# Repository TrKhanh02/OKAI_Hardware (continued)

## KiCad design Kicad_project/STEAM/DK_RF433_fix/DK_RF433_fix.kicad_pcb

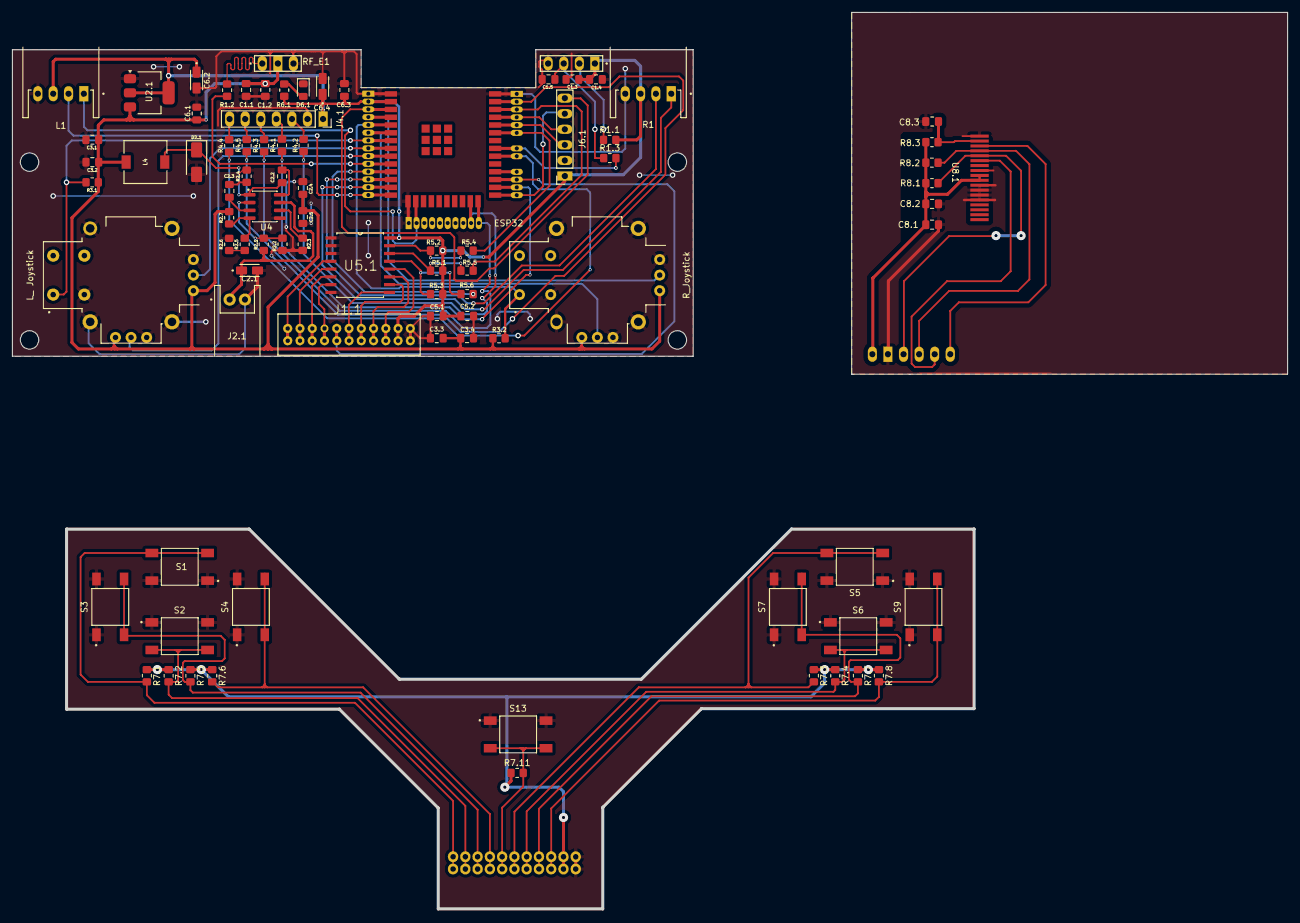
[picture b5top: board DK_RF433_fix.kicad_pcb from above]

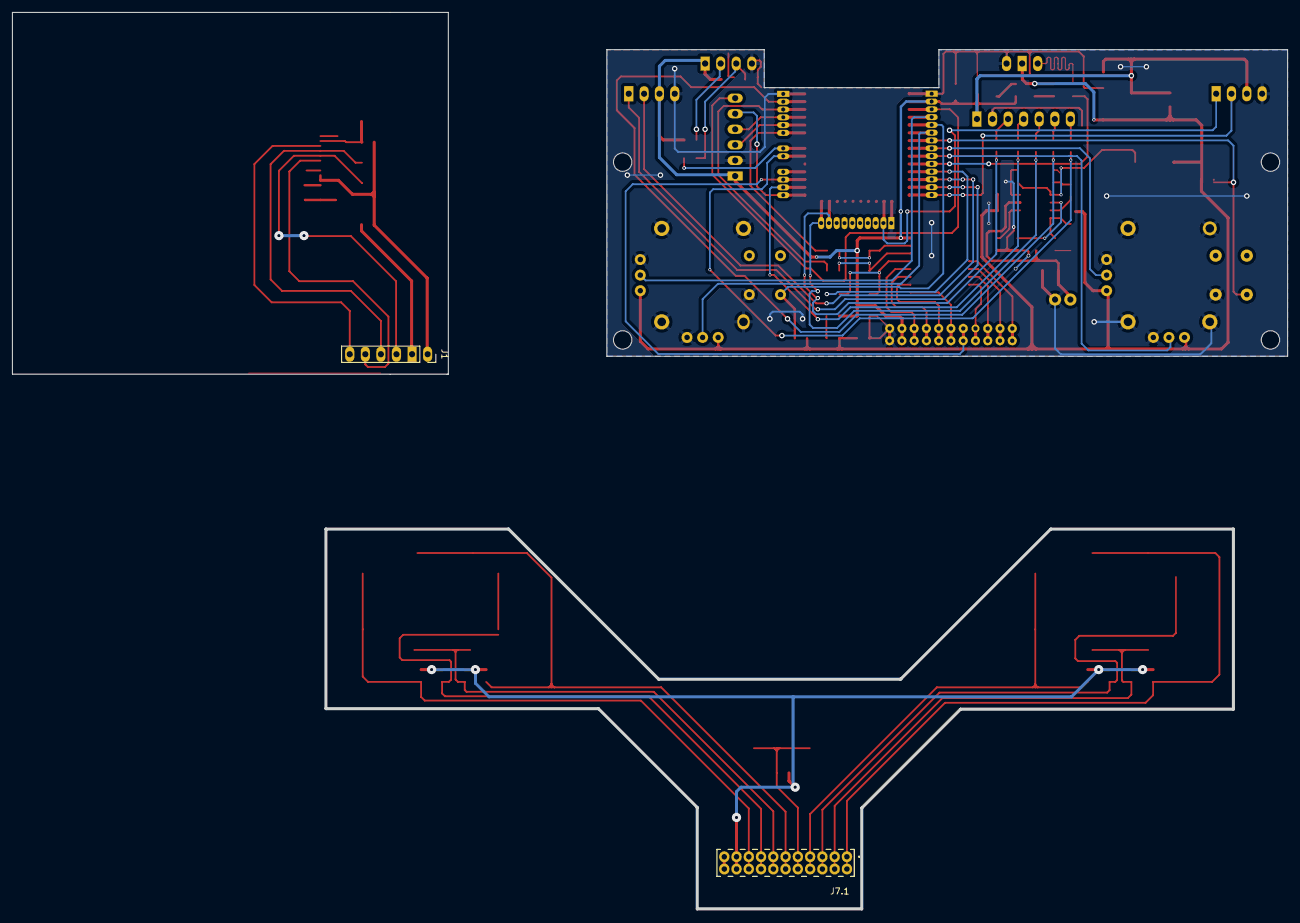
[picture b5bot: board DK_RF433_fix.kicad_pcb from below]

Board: 2 copper layers, 207.9 x 146.2 mm, 88 parts (2 on the bottom side), 75 nets.

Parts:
C1.1, C1.3, C2.4, C2.5, C3.1, C3.3, C5.1, C6.1, C8.1: 10uF; C_0805_2012Metric_Pad1.18x1.45mm_HandSolder
C1.2, C1.4, C1.5, C3.2, C3.4, C5.2, C6.3, C8.2, C8.3: 104; C_0805_2012Metric_Pad1.18x1.45mm_HandSolder
C2.1: 10uF; CAPMP3216X180N
C2.2: 100nF; C_0805_2012Metric_Pad1.18x1.45mm_HandSolder
C2.3: 151pF; C_0805_2012Metric_Pad1.18x1.45mm_HandSolder
C6.2: 22uF; CAPMP3216X180N
C6.4: TAJA106K016RNJ; CAPMP3216X180N
D2.1: SS34; D_SMA
D6.1: LED_Small_Filled; LED_0805_2012Metric_Pad1.15x1.40mm_HandSolder
J1: Conn_01x06_Pin; PinSocket_1x06_P2.54mm_Vertical
J1.1: button; SAMTEC-SQW-111-01-X-D
J1.2: RF433_GPS; SAMTEC_MTSW-104-12-T-S-740
J2.1: Vin; JST_S2B-XH-A
J4.1: LCD; PinSocket_1x07_P2.54mm_Vertical
J6.1: boot; PinSocket_1x06_P2.54mm_Vertical
J6.2: ESP32; J header esp32
J7.1: MTMM-111-04-L-D-187; SAMTEC_MTMM-111-04-L-D-187
L1: L1; JST_S4B-XH-A-1
L4: SLF7032T-331MR22-2PF; IND_SLF7032T-331MR22-2PF
R1: R2; JST_S4B-XH-A-1
R1.1, R2.5, R2.6, R5.1, R5.2, R5.3, R6.1, R8.1, R8.2, R8.3: 10K; R_0805_2012Metric_Pad1.20x1.40mm_HandSolder
R1.2, R1.3, R4.1, R4.2, R4.3, R4.4, R4.5, R5.4, R5.5, R5.6: 0R; R_0805_2012Metric_Pad1.20x1.40mm_HandSolder
R2.1: 100K; R_0805_2012Metric_Pad1.20x1.40mm_HandSolder
R2.2, R2.3, R2.4, R2.7: 100k; R_0805_2012Metric_Pad1.20x1.40mm_HandSolder
R3.1, R3.2, R7.1, R7.2, R7.3, R7.4, R7.5, R7.6, R7.7, R7.8, R7.11: 10k; R_0805_2012Metric_Pad1.20x1.40mm_HandSolder
RF_E1: U5; SAMTEC_MTSW-103-10-S-S-580
S1, S2, S3, S4, S5, S6, S7, S9, S13: FSM2JSMLTR; SW_1571527-2
U2.1: AMS1117-3.3; SOT-223-3_TabPin2
U4: MP1584EN; SOIC127P600X170-9N
U5.1: PCF8574T; SOIC127P1032X265-16N
U7.1: L_ Joystick; XDCR_COM-09032
U7.2: R_Joystick; XDCR_COM-09032
U8.1: Pad_18P_0.8

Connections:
/3.3: C8.1.2, C8.2.2, J1.1, R8.1.1, R8.2.1, R8.3.1, U8.1.09, U8.1.10
/3.3V: C1.3.2, C1.4.2, C5.1.1, C5.2.1, C6.2.1, C6.3.1, C6.4.1, J1.1.19, J1.1.20, J1.2.01, J4.1.1, J6.1.1, J6.2.2, L1.3, R1.3, R1.1.2, R5.1.1, R5.2.1, R5.3.1, R6.1.1, U2.1.2 (VO), U5.1.16 (VDD)
/3V3: J7.1.19, J7.1.20, R7.1.1, R7.2.1, R7.3.1, R7.4.1, R7.5.1, R7.6.1, R7.7.1, R7.8.1, R7.11.1
/5V: C1.1.1, C1.2.1, C2.4.2, C2.5.2, C3.1.1, C3.2.1, C3.3.1, C3.4.1, C6.1.1, L4.2, R2.7.2, R3.1.1, R3.2.1, RF_E1.02, U2.1.3 (VI), U7.1.H1 (H+), U7.1.V1 (V+), U7.2.H1 (H+), U7.2.V1 (V+)
/8.4V_B: C2.1.1, J2.1.1, R2.1.1, U4.7 (VIN)
/A1: J1.1.11, J1.1.12, U5.1.9 (P4)
/A2: J7.1.11, J7.1.12, R7.3.2, S5.3, S5.4
/B1: J1.1.13, J1.1.14, U5.1.10 (P5)
/B2: J7.1.13, J7.1.14, R7.4.2, S6.3, S6.4
/C1: J1.1.15, J1.1.16, U5.1.11 (P6)
/C2: J7.1.15, J7.1.16, R7.7.2, S7.3, S7.4
/CS: J1.3, R8.1.2, U8.1.05
/D1: J1.1.17, J1.1.18, U5.1.12 (P7)
/D2: J7.1.17, J7.1.18, R7.8.2, S9.3, S9.4
/DC: J1.4, R8.2.2, U8.1.04
/DOWN1: J1.1.3, J1.1.4, U5.1.5 (P1)
/DOWN2: J7.1.03, J7.1.04, R7.2.2, S2.3, S2.4
/Data_DC: R1.2.1, RF_E1.01
/EN: J6.1.6, J6.2.3
/G1: J6.2.12, R1.2
/H1: J6.2.16, L1.1
/I1: J6.2.13, R1.1
/INT: R5.3.2, R5.6.2, U5.1.13 (~INT)
/IO0: J6.1.5, J6.2.25
/IO2: J6.2.24, R4.3.2
/IO4: J6.2.26, R4.1.2
/IO12: J6.2.14, L1.2
/IO15: J6.2.23, R4.2.2
/IO16: J1.1.9, J1.1.10, J6.2.27
/IO18: J6.2.30, R4.4.2
/IO19: J6.2.31, R1.3.2
/IO21: J6.2.33, R5.4.1
/IO22: J6.2.36, R5.5.1
/IO23: J6.2.37, R4.5.2
/IO25: J6.2.10, R1.2.2
/IO26: J6.2.11, R5.6.1
/IO32: J6.2.8, U7.1.H2 (H)
/IO33: J6.2.9, U7.1.V2 (V)
/IO34: J6.2.6, U7.2.V2 (V)
/IO35: J6.2.7, R3.1.2, U7.1.B1A (SEL+)
/IO36: J6.2.4, U7.2.H2 (H)
/IO39: J6.2.5, R3.2.2, U7.2.B1A (SEL+)
/LCD_CLK: J4.1.7, R4.4.1
/LCD_CS: J4.1.3, R4.2.1
/LCD_DC: J4.1.5, R4.3.1
/LCD_MOSI: J4.1.6, R4.5.1
/LCD_RESET: J4.1.4, R4.1.1
/LEFT1: J1.1.5, J1.1.6, U5.1.6 (P2)
/LEFT2: J7.1.05, J7.1.06, R7.5.2, S3.3, S3.4
/MCU_RXD0: J6.1.3, J6.2.34
/MCU_TXD0: J6.1.4, J6.2.35
/MOSI: J1.5, U8.1.06
/PCF_SCL: R5.1.2, R5.5.2, U5.1.14 (SCL)
/PCF_SDA: R5.2.2, R5.4.2, U5.1.15 (SDA)
/RF_DATA_GPS: C1.5.1, J1.2.03, R1.3.1
/RIGHT1: J1.1.7, J1.1.8, U5.1.7 (P3)
/RIGHT2: J7.1.07, J7.1.08, R7.6.2, S4.3, S4.4
/RST: C8.3.2, R8.3.2, U8.1.02
/SCL: J1.6, U8.1.03
/UP1: J1.1.1, J1.1.2, U5.1.4 (P0)
/UP2: J7.1.01, J7.1.02, R7.1.2, S1.3, S1.4
/nutnguon2: J7.1.09, J7.1.10, R7.11.2, S13.3, S13.4
GND: C1.1.2, C1.2.2, C1.3.1, C1.4.1, C1.5.2, C2.1.2, C2.4.1, C2.5.1, C3.1.2, C3.2.2, C3.3.2, C3.4.2, C5.1.2, C5.2.2, C6.1.2, C6.2.2, C6.3.2, C6.4.2, D2.1.2 (A), D6.1.1 (K), J1.1.21, J1.1.22, J1.2.04, J2.1.2, J4.1.2, J6.1.2, J6.2.1, J6.2.15, J6.2.38, L1.4, R1.4, R2.2.2, R2.3.2, R2.4.2, R2.6.2, RF_E1.03, U2.1.1 (GND), U4.5 (GND), U5.1.1 (A0), U5.1.2 (A1), U5.1.3 (A2), U5.1.8 (VSS), U7.1.B2A (SEL-), U7.1.H3 (H-), U7.1.S1 (SHIELD), U7.1.S2 (SHIELD), U7.1.S3 (SHIELD), U7.1.S4 (SHIELD), U7.1.V3 (V-), U7.2.B2A (SEL-), U7.2.H3 (H-), U7.2.S1 (SHIELD), U7.2.S2 (SHIELD), U7.2.S3 (SHIELD), U7.2.S4 (SHIELD), U7.2.V3 (V-)
GND1: J7.1.21, J7.1.22, S1.1, S1.2, S2.1, S2.2, S3.1, S3.2, S4.1, S4.2, S5.1, S5.2, S6.1, S6.2, S7.1, S7.2, S9.1, S9.2, S13.1, S13.2
GND4: C8.1.1, C8.2.1, C8.3.1, J1.2, U8.1.01, U8.1.08, U8.1.11, U8.1.12, U8.1.13, U8.1.14
unnamed: C2.3.2, R2.4.1
unnamed: C2.2.2, D2.1.1 (K), L4.1, U4.1 (SW)
unnamed: D6.1.2 (A), R6.1.2
unnamed: J1.2.02, R1.1.1
unnamed: R2.5.2, R2.6.1
unnamed: C2.2.1, U4.8 (BST)
unnamed: C2.3.1, U4.3 (COMP)
unnamed: R2.1.2, R2.2.1, U4.2 (EN)
unnamed: R2.5.1, R2.7.1, U4.4 (FB)
unnamed: R2.3.1, U4.6 (FREQ)

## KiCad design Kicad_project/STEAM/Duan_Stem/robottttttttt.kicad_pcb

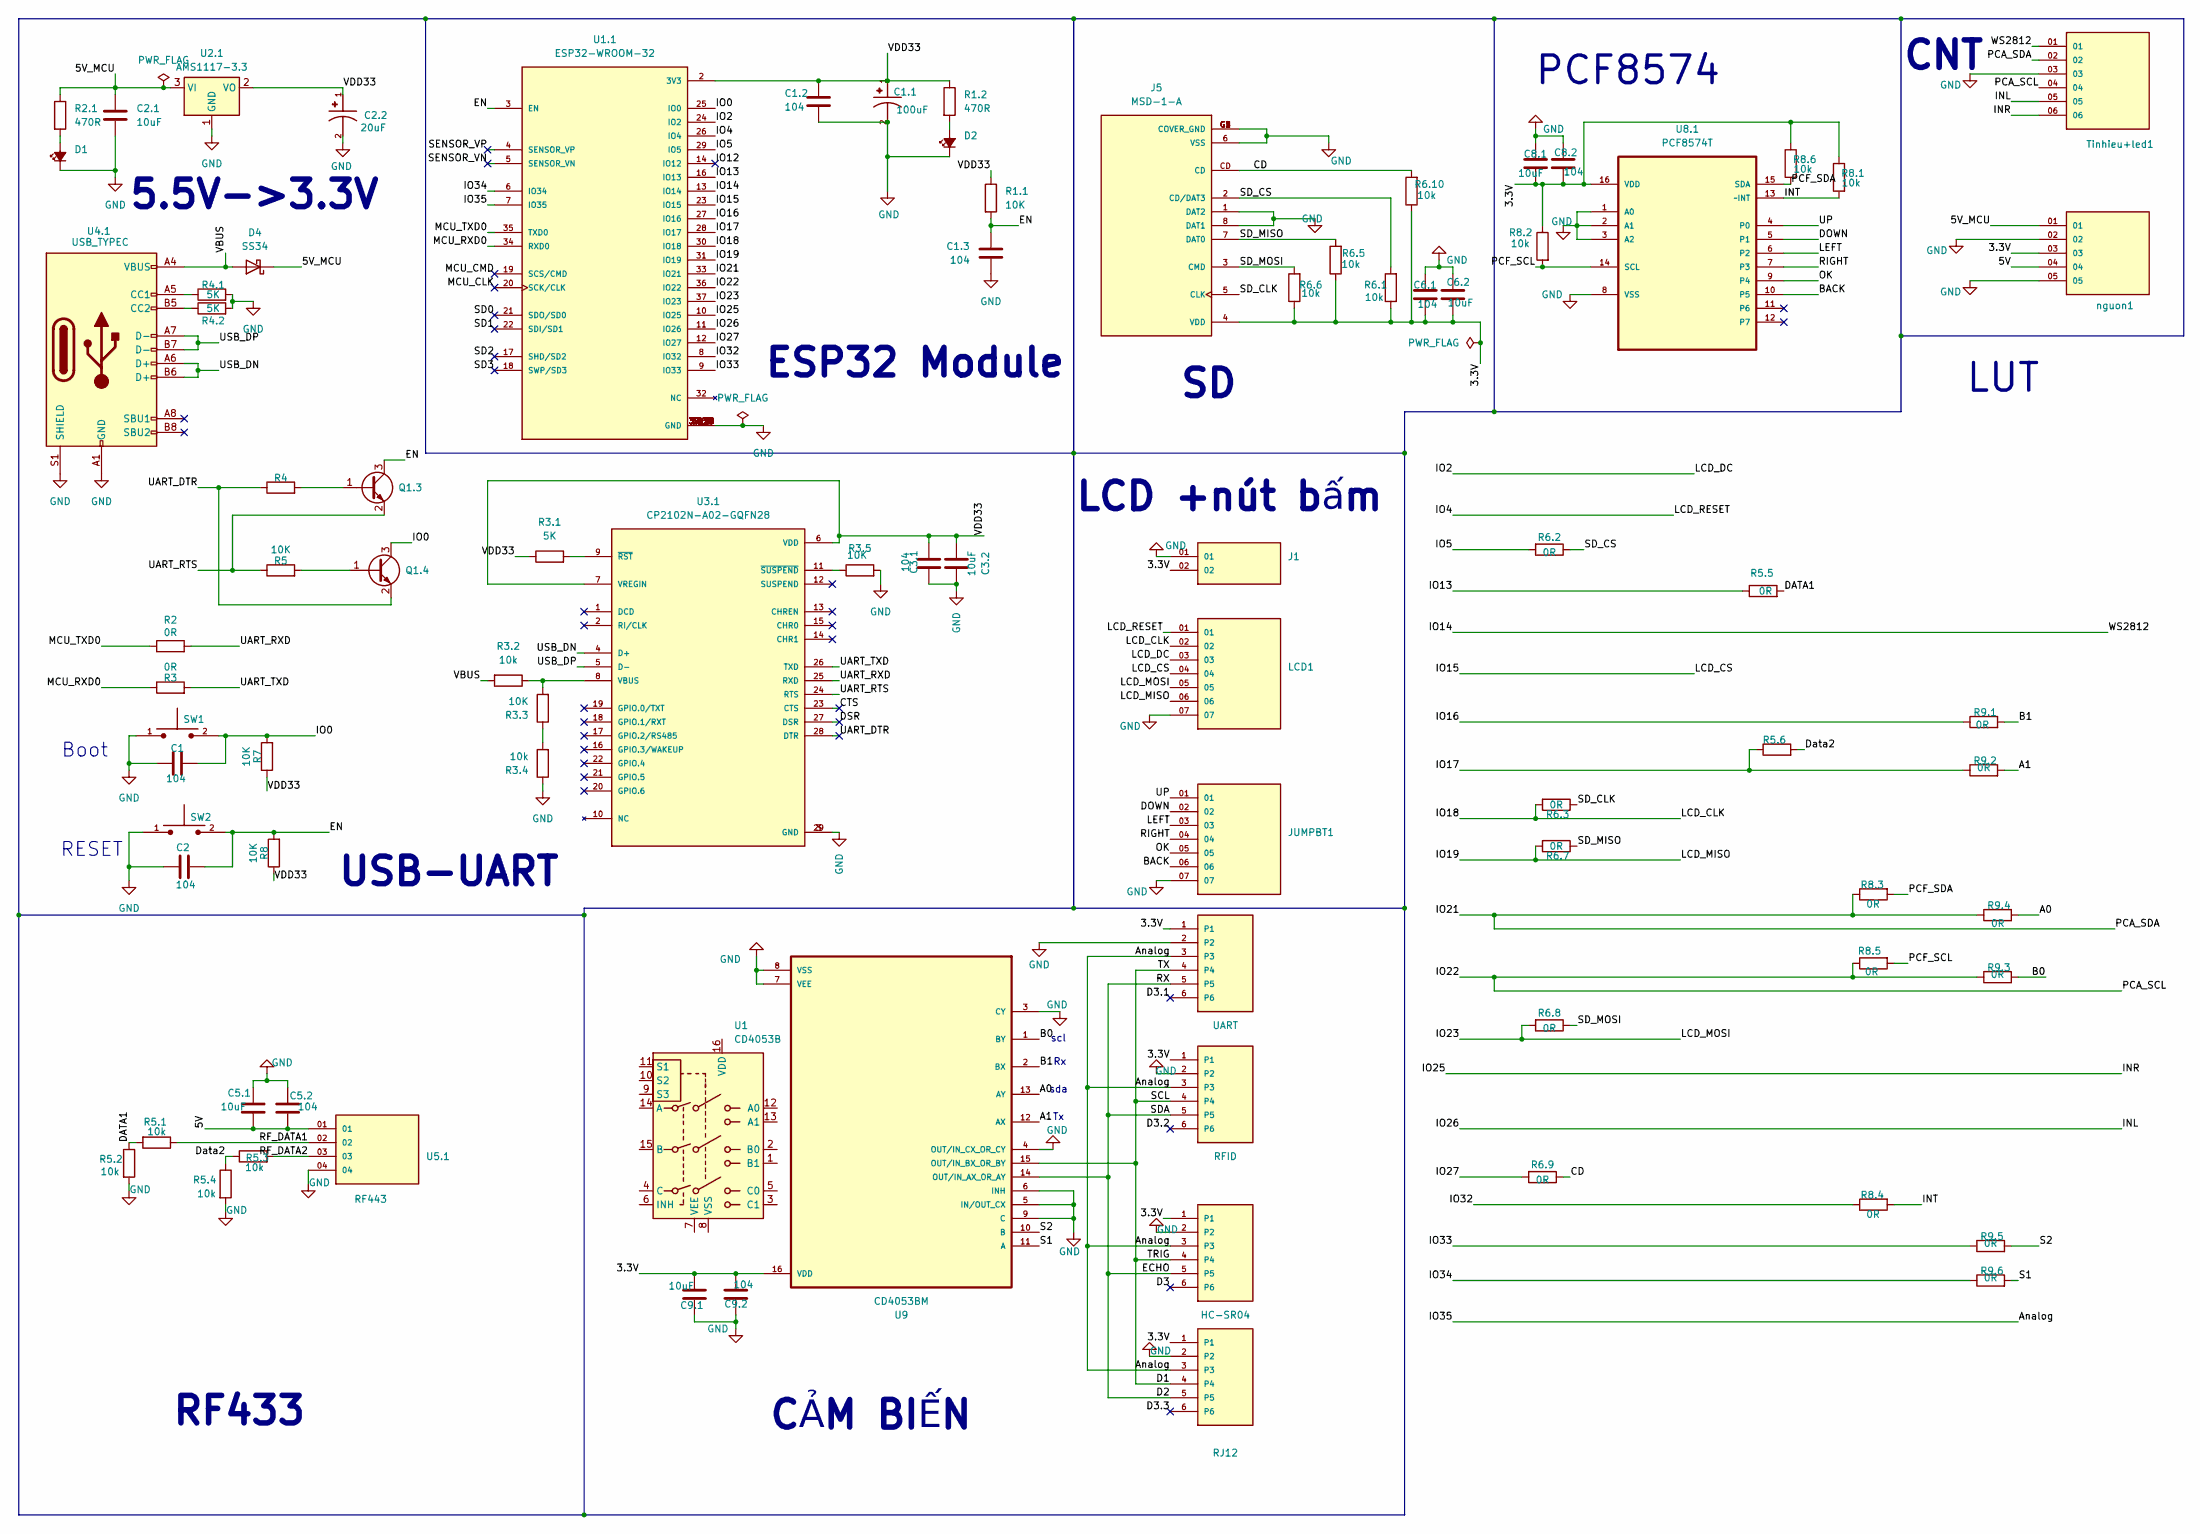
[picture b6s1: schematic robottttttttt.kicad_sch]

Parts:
C1, C1.2, C1.3, C2, C3.1, C5.2, C6.1, C8.2, C9.2: 104; C_0805_2012Metric_Pad1.18x1.45mm_HandSolder
C1.1: 100uF; CAPMP3216X180N; PARTREV 031320
C2.1, C3.2, C5.1, C6.2, C8.1, C9.1: 10uF; C_0805_2012Metric_Pad1.18x1.45mm_HandSolder
C2.2: 20uF; CAPMP3216X180N; PARTREV 031320
D1, D2: LED_Small_Filled; LED_0805_2012Metric_Pad1.15x1.40mm_HandSolder
D4: SS34; D_SMA
J1: TSW-102-23-T-S; SAMTEC_TSW-102-23-T-S; PARTREV R
J5: MSD-1-A; CUI_MSD-1-A; PARTREV 1.0
JUMPBT1: MTLW-107-24-G-S-280; SAMTEC_MTLW-107-24-G-S-280; PARTREV R
LCD1: MTLW-107-24-G-S-280; SAMTEC_MTLW-107-24-G-S-280; PARTREV R
Q1.3, Q1.4: SS8050; SOT-23
R1: RFID; TE_RJ11-6N-B; PART_DESCRIPTION CONN MOD JACK 6P6C R/A UNSHLD
R1.1, R3.3, R3.5, R4, R5, R7, R8: 10K; R_0805_2012Metric_Pad1.20x1.40mm_HandSolder
R1.2, R2.1: 470R; R_0805_2012Metric_Pad1.20x1.40mm_HandSolder
R2, R3, R5.5, R5.6, R6.2, R6.3, R6.7, R6.8, R6.9, R8.3, R8.4, R8.5, R9.1, R9.2, R9.3, R9.4, R9.5, R9.6: 0R; R_0805_2012Metric_Pad1.20x1.40mm_HandSolder
R3.1, R4.1, R4.2: 5K; R_0805_2012Metric_Pad1.20x1.40mm_HandSolder
R3.2, R3.4, R5.1, R5.2, R5.3, R5.4, R6.1, R6.5, R6.6, R6.10, R8.1, R8.2, R8.6: 10k; R_0805_2012Metric_Pad1.20x1.40mm_HandSolder
R6: UART; TE_RJ11-6N-B; PART_DESCRIPTION CONN MOD JACK 6P6C R/A UNSHLD
RF443: U5.1; SAMTEC_MTSW-104-12-T-S-740; PARTREV R
RJ11, RJ12: HC-SR04; TE_RJ11-6N-B; PART_DESCRIPTION CONN MOD JACK 6P6C R/A UNSHLD
SW1, SW2: TS10-63-26-BE-250-SMT-TR; SW_TS10-63-26-BE-250-SMT-TR; PARTREV 1.0
Tinhieu+led1: MTSW-106-08-L-S-295; SAMTEC_MTSW-106-08-L-S-295; PARTREV R
U1: CD4053B
U1.1: ESP32-WROOM-32; MODULE_ESP32-WROOM-32
U2.1: AMS1117-3.3; SOT-223-3_TabPin2
U3.1: CP2102N-A02-GQFN28; QFN50P500X500X80-29N; PARTREV 1.5
U4.1: USB_TYPEC; USB_C_Receptacle_HRO_TYPE-C-31-M-12
U8.1: PCF8574T; SOIC127P1032X265-16N; MPN PCF8574T
U9: CD4053BM; SOIC127P600X175-16N
nguon1: TSW-105-17-T-S; SAMTEC_TSW-105-17-T-S; PARTREV R

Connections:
/3.3V: C6.1.1, C6.2.1, C8.1.1, C8.2.1, C9.1.1, C9.2.1, J1.02, J5.4 (VDD), R1.1, R6.1, R6.1.1, R6.5.1, R6.6.1, R6.10.1, R8.1.1, R8.2.1, R8.6.1, RJ11.1, RJ12.1, U8.1.16 (VDD), U9.16 (VDD), nguon1.03
/5V: C5.1.2, C5.2.2, RF443.01, nguon1.04
/5V_MCU: C2.1.1, D4.1 (K), R2.1.1, U2.1.3 (VI), nguon1.01
/A0: R9.4.2, U9.13 (AY)
/A1: R9.2.2, U9.12 (AX)
/Analog: R1.3, R6.3, RJ11.3, RJ12.3, U1.1.7 (IO35)
/B0: R9.3.2, U9.1 (BY)
/B1: R9.1.2, U9.2 (BX)
/BACK: JUMPBT1.06, U8.1.10 (P5)
/CD: J5.CD, R6.9.1, R6.10.2
/CTS: U3.1.23 (CTS)
/D1: R1.4, R6.4, RJ11.4, RJ12.4, U9.15 (OUT/IN_BX_OR_BY)
/D2: R1.5, R6.5, RJ11.5, RJ12.5, U9.14 (OUT/IN_AX_OR_AY)
/D3: RJ11.6
/D3.1: R6.6
/D3.2: R1.6
/D3.3: RJ12.6
/DATA1: R5.1.2, R5.2.1, R5.5.2
/DOWN: JUMPBT1.02, U8.1.5 (P1)
/DSR: U3.1.27 (DSR)
/Data2: R5.3.1, R5.4.1, R5.6.2
/EN: C1.3.1, C2.2, Q1.3.3 (C), R1.1.2, R8.2, SW2.2, U1.1.3 (EN)
/INL: Tinhieu+led1.05, U1.1.11 (IO26)
/INR: Tinhieu+led1.06, U1.1.10 (IO25)
/INT: R8.1.2, R8.4.2, U8.1.13 (~INT)
/IO0: C1.2, Q1.4.3 (C), R7.2, SW1.2, U1.1.25 (IO0)
/IO2: LCD1.03, U1.1.24 (IO2)
/IO4: LCD1.01, U1.1.26 (IO4)
/IO5: R6.2.2, U1.1.29 (IO5)
/IO12: U1.1.14 (IO12)
/IO13: R5.5.1, U1.1.16 (IO13)
/IO14: Tinhieu+led1.01, U1.1.13 (IO14)
/IO15: LCD1.04, U1.1.23 (IO15)
/IO16: R9.1.1, U1.1.27 (IO16)
/IO17: R5.6.1, R9.2.1, U1.1.28 (IO17)
/IO18: LCD1.02, R6.3.2, U1.1.30 (IO18)
/IO19: LCD1.06, R6.7.2, U1.1.31 (IO19)
/IO21: R8.3.1, R9.4.1, Tinhieu+led1.02, U1.1.33 (IO21)
/IO22: R8.5.1, R9.3.1, Tinhieu+led1.04, U1.1.36 (IO22)
/IO23: LCD1.05, R6.8.2, U1.1.37 (IO23)
/IO27: R6.9.2, U1.1.12 (IO27)
/IO32: R8.4.1, U1.1.8 (IO32)
/IO33: R9.5.1, U1.1.9 (IO33)
/IO34: R9.6.1, U1.1.6 (IO34)
/LEFT: JUMPBT1.03, U8.1.6 (P2)
/MCU_CLK: U1.1.20 (SCK/CLK)
/MCU_CMD: U1.1.19 (SCS/CMD)
/MCU_RXD0: R3.1, U1.1.34 (RXD0)
/MCU_TXD0: R2.1, U1.1.35 (TXD0)
/OK: JUMPBT1.05, U8.1.9 (P4)
/PCF_SCL: R8.2.2, R8.5.2, U8.1.14 (SCL)
/PCF_SDA: R8.3.2, R8.6.2, U8.1.15 (SDA)
/RF_DATA1: R5.1.1, RF443.02
/RF_DATA2: R5.3.2, RF443.03
/RIGHT: JUMPBT1.04, U8.1.7 (P3)
/S1: R9.6.2, U9.11 (A)
/S2: R9.5.2, U9.10 (B)
/SD0: U1.1.21 (SDO/SD0)
/SD1: U1.1.22 (SDI/SD1)
/SD2: U1.1.17 (SHD/SD2)
/SD3: U1.1.18 (SWP/SD3)
/SD_CLK: J5.5 (CLK), R6.3.1
/SD_CS: J5.2 (CD/DAT3), R6.1.2, R6.2.1
/SD_MISO: J5.7 (DAT0), R6.5.2, R6.7.1
/SD_MOSI: J5.3 (CMD), R6.6.2, R6.8.1
/SENSOR_VN: U1.1.5 (SENSOR_VN)
/SENSOR_VP: U1.1.4 (SENSOR_VP)
/UART_DTR: Q1.4.2 (E), R4.1, U3.1.28 (DTR)
/UART_RTS: Q1.3.2 (E), R5.1, U3.1.24 (RTS)
/UART_RXD: R2.2, U3.1.25 (RXD)
/UART_TXD: R3.2, U3.1.26 (TXD)
/UP: JUMPBT1.01, U8.1.4 (P0)
/USB_DN: U3.1.4 (D+), U4.1.A6 (D+), U4.1.B6 (D+)
/USB_DP: U3.1.5 (D-), U4.1.A7 (D-), U4.1.B7 (D-)
/VBUS: D4.2 (A), R3.2.2, U4.1.A4 (VBUS), U4.1.A9 (VBUS), U4.1.B4 (VBUS), U4.1.B9 (VBUS)
/VDD33: C1.1.1, C1.2.1, C2.2.1, C3.1.2, C3.2.2, R1.1.1, R1.2.1, R3.1.1, R7.1, R8.1, U1.1.2 (3V3), U2.1.2 (VO), U3.1.6 (VDD), U3.1.7 (VREGIN)
GND: C1.1, C1.1.2, C1.2.2, C1.3.2, C2.1, C2.1.2, C2.2.2, C3.1.1, C3.2.1, C5.1.1, C5.2.1, C6.1.2, C6.2.2, C8.1.2, C8.2.2, C9.1.2, C9.2.2, D1.1 (K), D2.1 (K), J1.01, J5.1 (DAT2), J5.6 (VSS), J5.8 (DAT1), J5.G1 (COVER_GND), J5.G2 (COVER_GND), J5.G3 (COVER_GND), J5.G4 (COVER_GND), JUMPBT1.07, LCD1.07, R1.2, R3.4.1, R3.5.2, R4.1.2, R4.2.2, R5.2.2, R5.4.2, R6.2, RF443.04, RJ11.2, RJ12.2, SW1.1, SW2.1, Tinhieu+led1.03, U1.1.1 (GND), U1.1.15 (GND), U1.1.38 (GND), U1.1.39_1 (GND), U1.1.39_2 (GND), U1.1.39_3 (GND), U1.1.39_4 (GND), U1.1.39_5 (GND), U1.1.39_6 (GND), U1.1.39_7 (GND), U1.1.39_8 (GND), U1.1.39_9 (GND), U1.1.39_10 (GND), U1.1.39_11 (GND), U1.1.39_12 (GND), U1.1.39_13 (GND), U1.1.39_14 (GND), U1.1.39_15 (GND), U1.1.39_16 (GND), U1.1.39_17 (GND), U1.1.39_18 (GND), U1.1.39_19 (GND), U1.1.39_20 (GND), U1.1.39_21 (GND), U2.1.1 (GND), U3.1.3 (GND), U3.1.29 (GND), U4.1.A1 (GND), U4.1.A12 (GND), U4.1.B1 (GND), U4.1.B12 (GND), U4.1.S1 (SHIELD), U8.1.1 (A0), U8.1.2 (A1), U8.1.3 (A2), U8.1.8 (VSS), U9.3 (CY), U9.4 (OUT/IN_CX_OR_CY), U9.5 (IN/OUT_CX), U9.6 (INH), U9.7 (VEE), U9.8 (VSS), U9.9 (C), nguon1.02, nguon1.05
unnamed: D1.2 (A), R2.1.2
unnamed: D2.2 (A), R1.2.2
unnamed: Q1.3.1 (B), R4.2
unnamed: Q1.4.1 (B), R5.2
unnamed: R3.3.1, R3.4.2
unnamed: R3.2.1, R3.3.2, U3.1.8 (VBUS)
unnamed: R3.1.2, U3.1.9 (~RST)
unnamed: R3.5.1, U3.1.11 (~SUSPEND)
unnamed: R4.1.1, U4.1.A5 (CC1)
unnamed: R4.2.1, U4.1.B5 (CC2)

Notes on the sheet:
ESP32 Module
RESET
5.5V->3.3V
sda
CẢM BIẾN
RF433
PCF8574
LCD +nút bấm
CNT
LUT
Boot
USB-UART
scl

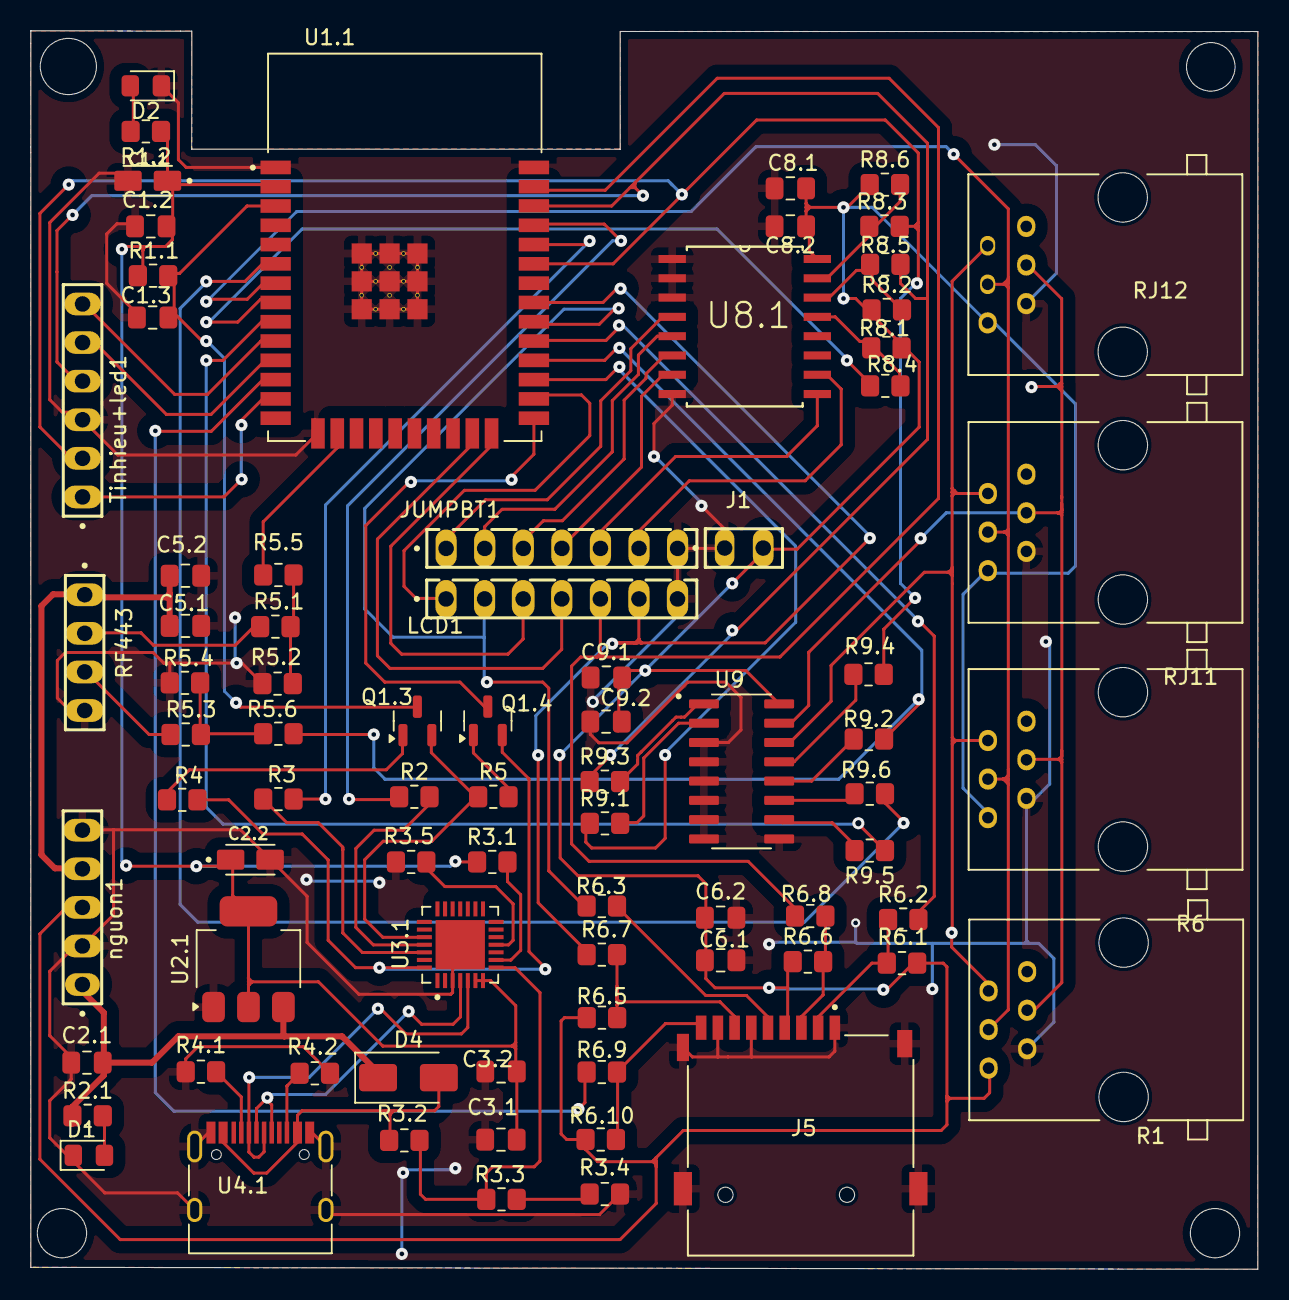
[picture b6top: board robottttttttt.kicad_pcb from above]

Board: 2 copper layers, 80.8 x 81.5 mm, 78 parts (0 on the bottom side), 72 nets.
